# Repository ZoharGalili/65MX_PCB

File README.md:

# The65MX Keyboard PCB

a 65% keyboard pcb for use with my future keyboard projects.

## Features

### big components and BAV-70 diodes

I plan to assemble the pcb by hand to save costs as I have no problem putting the time to solder commponents by hand. for this reason i chose to not have any footprints smaller than an 0805 and also use BAV-70 dual diodes as i belive it will take less time to solder a single BAV-70 than two standard diodes.

### JST_SH daughterboard connector

I like the UBD-S daughterboard for case design but I have learned from a previous keyboard project that the molex EZmate connector is shit. I probably didnt solder it properly and it repeatedly snapped of the board. for this exact reason I desined the [UBD-S-JST](https://github.com/ZoharGalili/UDB-S-JST), a fork of the [UBD-S](https://github.com/Unified-Daughterboard/UDB-S) with a JST connecotr along with some ohter changes.

### QMK firmware and VIA support

the PCB uses an STM32f072 microcontroller. I have made a keyboard with this microcontroller before running QMK with VIA 

### bakeneko65 and ai03 vega board outline

I coppied the board outline of the bekeneko for supporting a gummy o-ring friction fit mount. I also took the board outline from the ai03 vega so the board can support an internally screwed case. 

### soldered MX switches

I have encountered problems before with the standard keilh hot swap sockets so i decided to make a solder pcb this time. mill max sockets exits so if I ever want to have a hotswap board I can pop those in.

### multilatout support

the board supports 6.25u or 7u spacebar, stepped caps lock and split backspace. this isnt the most layouts in a board but i feel like those are the layouts that I may want to use and I dont want to go crazy with layout support.

## board renders

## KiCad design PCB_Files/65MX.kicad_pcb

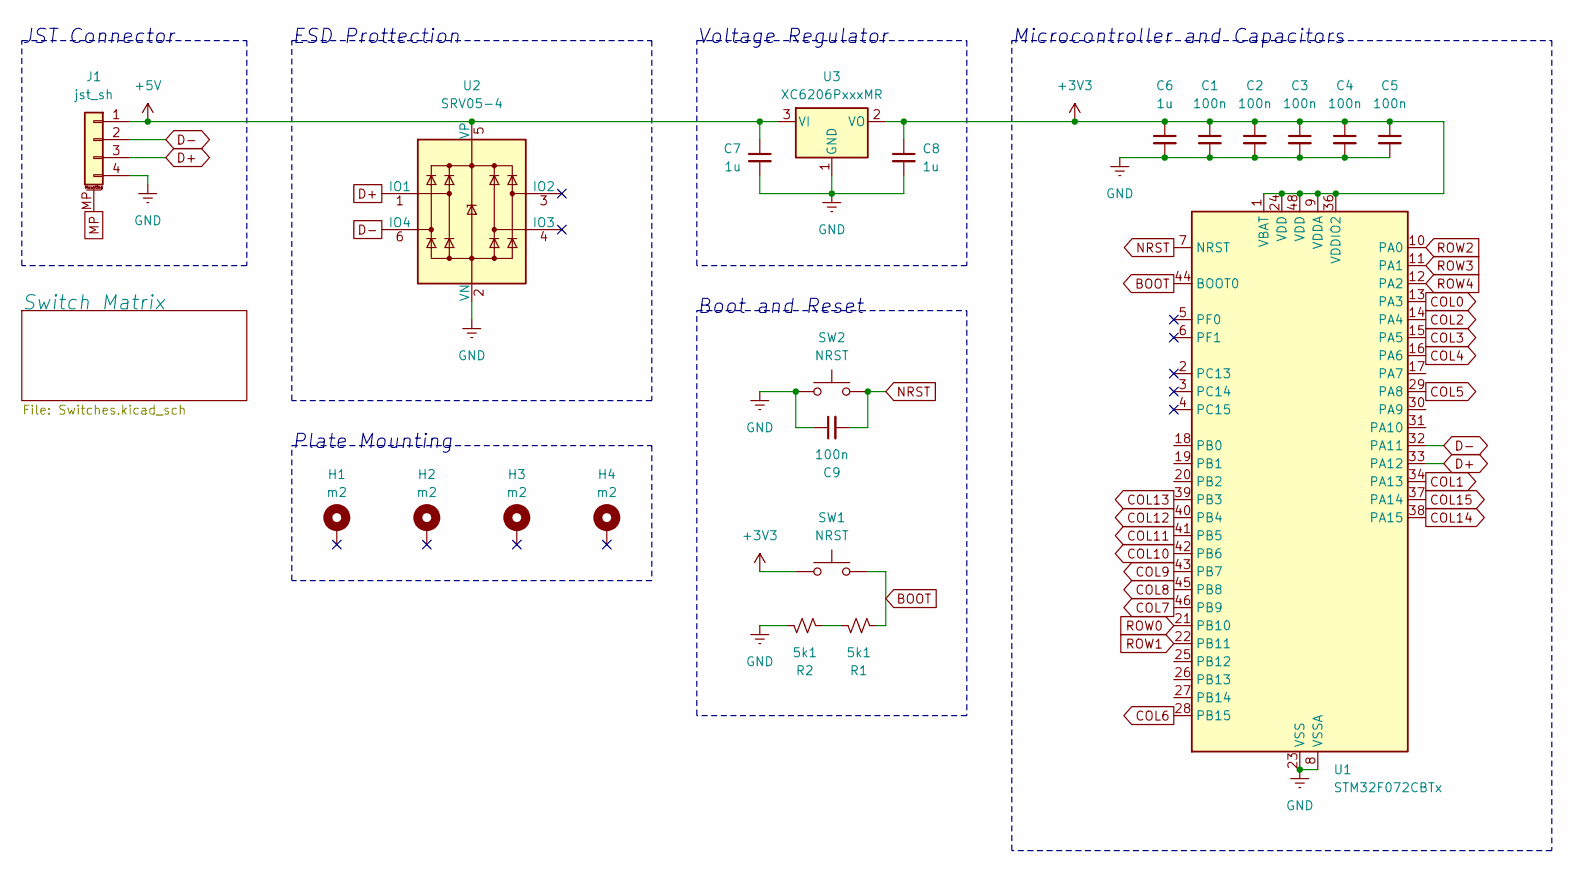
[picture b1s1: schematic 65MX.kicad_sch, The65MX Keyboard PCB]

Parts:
C1, C2, C3, C4, C5, C9: 100n; C_0805_2012Metric
C6, C7, C8: 1u; C_1206_3216Metric
H1, H2, H3, H4: m2; MountingHole_2.2mm_M2_Pad_TopBottom
J1: jst_sh; JST_SH_SM04B-SRSS-TB_1x04-1MP_P1.00mm_Horizontal
R1, R2: 5k1; R_0805_2012Metric
SW1, SW2: NRST; SW_SPST_SKQG_WithStem
U1: STM32F072CBTx; LQFP-48_7x7mm_P0.5mm
U2: SRV05-4; SOT-23-6-routable
U3: XC6206PxxxMR; SOT-23-3

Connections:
+3V3: C1.1, C2.1, C3.1, C4.1, C5.1, C6.1, C8.1, SW1.1, U1.1 (VBAT), U1.9 (VDDA), U1.24 (VDD), U1.36 (VDDIO2), U1.48 (VDD), U3.2 (VO)
+5V: C7.1, J1.1, U2.5 (VP), U3.3 (VI)
BOOT: R1.2, SW1.2, U1.44 (BOOT0)
COL0: U1.13 (PA3); also elsewhere on the board
COL1: U1.34 (PA13); also elsewhere on the board
COL2: U1.14 (PA4); also elsewhere on the board
COL3: U1.15 (PA5); also elsewhere on the board
COL4: U1.16 (PA6); also elsewhere on the board
COL5: U1.29 (PA8); also elsewhere on the board
COL6: U1.28 (PB15); also elsewhere on the board
COL7: U1.46 (PB9); also elsewhere on the board
COL8: U1.45 (PB8); also elsewhere on the board
COL9: U1.43 (PB7); also elsewhere on the board
COL10: U1.42 (PB6); also elsewhere on the board
COL11: U1.41 (PB5); also elsewhere on the board
COL12: U1.40 (PB4); also elsewhere on the board
COL13: U1.39 (PB3); also elsewhere on the board
COL14: U1.38 (PA15); also elsewhere on the board
COL15: U1.37 (PA14); also elsewhere on the board
D+: J1.3, U1.33 (PA12), U2.1 (IO1)
D-: J1.2, U1.32 (PA11), U2.6 (IO4)
GND: C1.2, C2.2, C3.2, C4.2, C5.2, C6.2, C7.2, C8.2, C9.1, J1.4, R2.1, SW2.1, U1.8 (VSSA), U1.23 (VSS), U1.35 (VSS), U1.47 (VSS), U2.2 (VN), U3.1 (GND)
MP: J1.MP (MountPin)
NRST: C9.2, SW2.2, U1.7 (NRST)
unnamed: R1.1, R2.2
ROW0: U1.21 (PB10); also elsewhere on the board
ROW1: U1.22 (PB11); also elsewhere on the board
ROW2: U1.10 (PA0); also elsewhere on the board
ROW3: U1.11 (PA1); also elsewhere on the board
ROW4: U1.12 (PA2); also elsewhere on the board

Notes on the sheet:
Microcontroller and Capacitors
Voltage Regulator
JST Connector
ESD Prottection
Plate Mounting
Boot and Reset

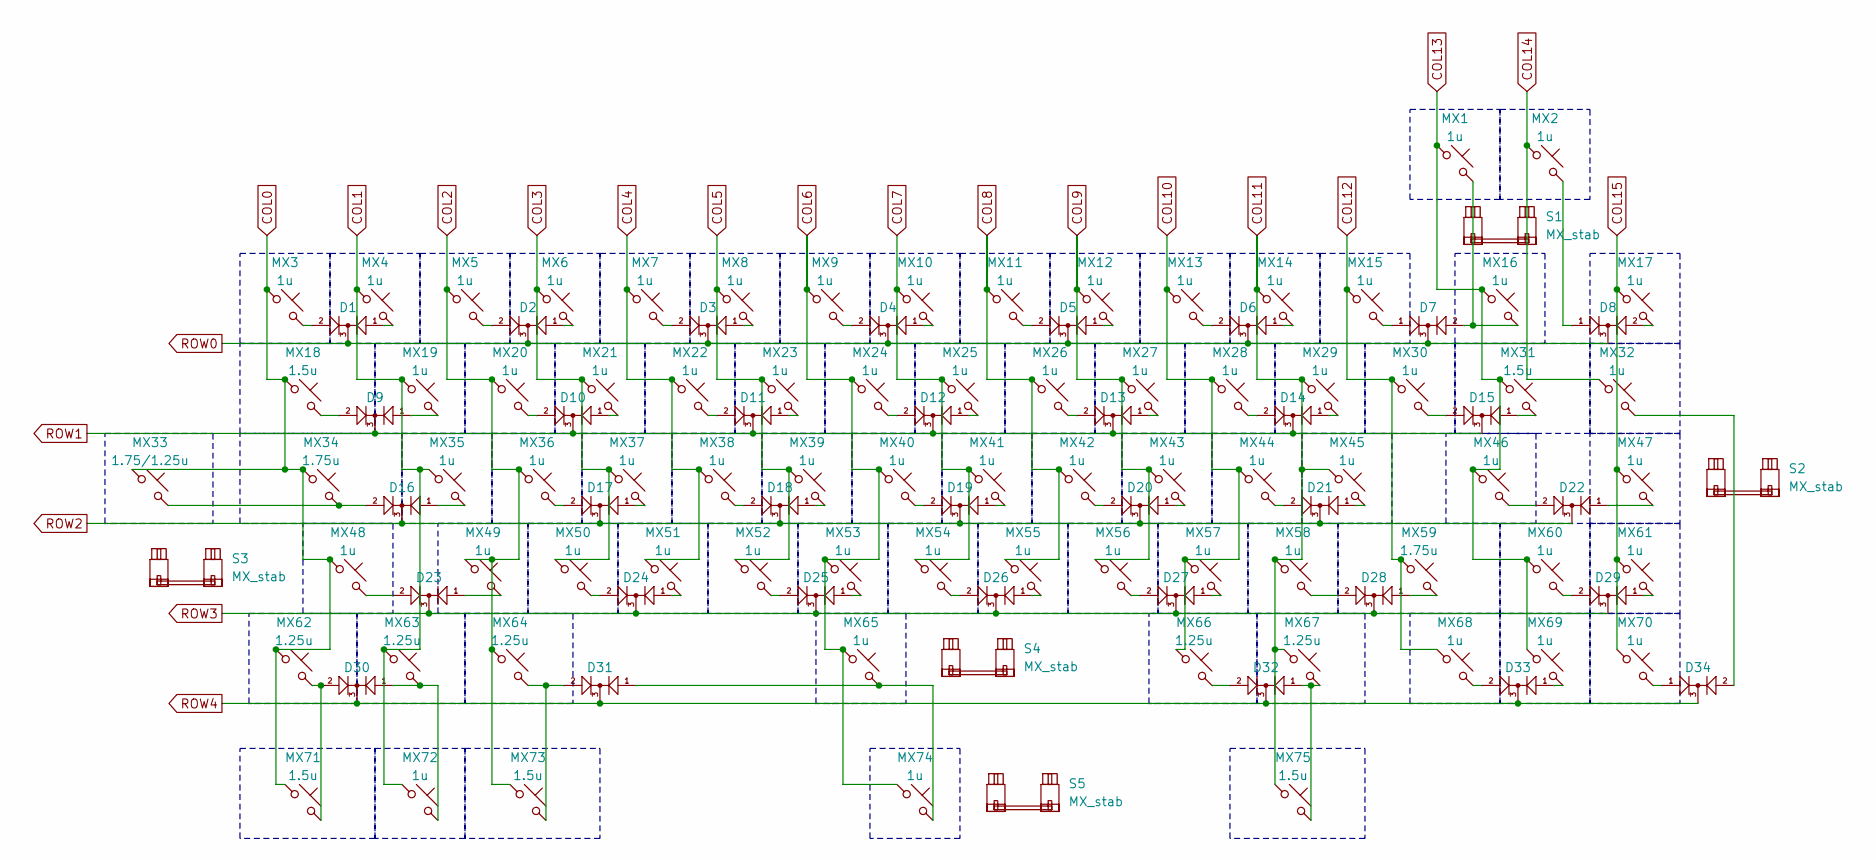
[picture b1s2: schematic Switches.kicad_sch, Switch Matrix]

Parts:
D1, D2, D3, D4, D5, D6, D7, D8, D9, D10, D11, D12, D13, D14, D15, D16, D17, D18, D19, D20, D21, D22, D23, D24, D25, D26, D27, D28, D29, D30, D31, D32, D33, D34: BAV70_Small; SOT-23
MX1, MX2, MX3, MX4, MX5, MX6, MX7, MX8, MX9, MX10, MX11, MX12, MX13, MX14, MX15, MX16, MX17, MX19, MX20, MX21, MX22, MX23, MX24, MX25, MX26, MX27, MX28, MX29, MX30, MX32, MX35, MX36, MX37, MX38, MX39, MX40, MX41, MX42, MX43, MX44, MX45, MX46, MX47, MX48, MX49, MX50, MX51, MX52, MX53, MX54, MX55, MX56, MX57, MX58, MX60, MX61, MX65, MX68, MX69, MX70, MX72, MX74: 1u; SW_MX_1u
MX18, MX31, MX71, MX73, MX75: 1.5u; SW_MX_1.5u
MX33: 1.75/1.25u; SW_MX_1.75u_STP_1.25
MX34, MX59: 1.75u; SW_MX_1.75u
MX62, MX63, MX64, MX66, MX67: 1.25u; SW_MX_1.25u
S1: MX_stab; STAB_MX_P_2u
S2, S3: MX_stab; STAB_MX_P_2.25u
S4: MX_stab; STAB_MX_P_6.25u
S5: MX_stab; STAB_MX_P_7u

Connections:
COL0: MX3.1, MX18.1, MX33.1, MX34.1, MX48.1, MX62.1, MX71.1; also elsewhere on the board
COL1: MX4.1, MX19.1, MX35.1, MX63.1, MX72.1; also elsewhere on the board
COL2: MX5.1, MX20.1, MX36.1, MX49.1, MX64.1, MX73.1; also elsewhere on the board
COL3: MX6.1, MX21.1, MX37.1, MX50.1; also elsewhere on the board
COL4: MX7.1, MX22.1, MX38.1, MX51.1; also elsewhere on the board
COL5: MX8.1, MX23.1, MX39.1, MX52.1; also elsewhere on the board
COL6: MX9.1, MX24.1, MX40.1, MX53.1, MX65.1, MX74.1; also elsewhere on the board
COL7: MX10.1, MX25.1, MX41.1, MX54.1; also elsewhere on the board
COL8: MX11.1, MX26.1, MX42.1, MX55.1; also elsewhere on the board
COL9: MX12.1, MX27.1, MX43.1, MX56.1; also elsewhere on the board
COL10: MX13.1, MX28.1, MX44.1, MX57.1, MX66.1; also elsewhere on the board
COL11: MX14.1, MX29.1, MX45.1, MX58.1, MX67.1, MX75.1; also elsewhere on the board
COL12: MX15.1, MX30.1, MX59.1, MX68.1; also elsewhere on the board
COL13: MX1.1, MX16.1, MX31.1, MX46.1, MX60.1, MX69.1; also elsewhere on the board
COL14: MX2.1, MX32.1; also elsewhere on the board
COL15: MX17.1, MX47.1, MX61.1, MX70.1; also elsewhere on the board
unnamed: D1.1 (A1), MX4.2
unnamed: D1.2 (A2), MX3.2
unnamed: D2.1 (A1), MX6.2
unnamed: D2.2 (A2), MX5.2
unnamed: D3.1 (A1), MX8.2
unnamed: D3.2 (A2), MX7.2
unnamed: D4.1 (A1), MX10.2
unnamed: D4.2 (A2), MX9.2
unnamed: D5.1 (A1), MX12.2
unnamed: D5.2 (A2), MX11.2
unnamed: D6.1 (A1), MX14.2
unnamed: D6.2 (A2), MX13.2
unnamed: D7.1 (A1), MX15.2
unnamed: D7.2 (A2), MX1.2, MX16.2
unnamed: D8.1 (A1), MX2.2
unnamed: D8.2 (A2), MX17.2
unnamed: D9.1 (A1), MX19.2
unnamed: D9.2 (A2), MX18.2
unnamed: D10.1 (A1), MX21.2
unnamed: D10.2 (A2), MX20.2
unnamed: D11.1 (A1), MX23.2
unnamed: D11.2 (A2), MX22.2
unnamed: D12.1 (A1), MX25.2
unnamed: D12.2 (A2), MX24.2
unnamed: D13.1 (A1), MX27.2
unnamed: D13.2 (A2), MX26.2
unnamed: D14.1 (A1), MX29.2
unnamed: D14.2 (A2), MX28.2
unnamed: D15.1 (A1), MX31.2
unnamed: D15.2 (A2), MX30.2
unnamed: D16.1 (A1), MX35.2
unnamed: D16.2 (A2), MX33.2, MX34.2
unnamed: D17.1 (A1), MX37.2
unnamed: D17.2 (A2), MX36.2
unnamed: D18.1 (A1), MX39.2
unnamed: D18.2 (A2), MX38.2
unnamed: D19.1 (A1), MX41.2
unnamed: D19.2 (A2), MX40.2
unnamed: D20.1 (A1), MX43.2
unnamed: D20.2 (A2), MX42.2
unnamed: D21.1 (A1), MX45.2
unnamed: D21.2 (A2), MX44.2
unnamed: D22.1 (A1), MX47.2
unnamed: D22.2 (A2), MX46.2
unnamed: D23.1 (A1), MX49.2
unnamed: D23.2 (A2), MX48.2
unnamed: D24.1 (A1), MX51.2
unnamed: D24.2 (A2), MX50.2
unnamed: D25.1 (A1), MX53.2
unnamed: D25.2 (A2), MX52.2
unnamed: D26.1 (A1), MX55.2
unnamed: D26.2 (A2), MX54.2
unnamed: D27.1 (A1), MX57.2
unnamed: D27.2 (A2), MX56.2
unnamed: D28.1 (A1), MX59.2
unnamed: D28.2 (A2), MX58.2
unnamed: D29.1 (A1), MX61.2
unnamed: D29.2 (A2), MX60.2
unnamed: D30.1 (A1), MX63.2, MX72.2
unnamed: D30.2 (A2), MX62.2, MX71.2
unnamed: D31.1 (A1), MX65.2, MX74.2
unnamed: D31.2 (A2), MX64.2, MX73.2
unnamed: D32.1 (A1), MX67.2, MX75.2
unnamed: D32.2 (A2), MX66.2
unnamed: D33.1 (A1), MX69.2
unnamed: D33.2 (A2), MX68.2
unnamed: D34.1 (A1), MX70.2
unnamed: D34.2 (A2), MX32.2
ROW0: D1.3 (K), D2.3 (K), D3.3 (K), D4.3 (K), D5.3 (K), D6.3 (K), D7.3 (K), D8.3 (K); also elsewhere on the board
ROW1: D9.3 (K), D10.3 (K), D11.3 (K), D12.3 (K), D13.3 (K), D14.3 (K), D15.3 (K); also elsewhere on the board
ROW2: D16.3 (K), D17.3 (K), D18.3 (K), D19.3 (K), D20.3 (K), D21.3 (K), D22.3 (K); also elsewhere on the board
ROW3: D23.3 (K), D24.3 (K), D25.3 (K), D26.3 (K), D27.3 (K), D28.3 (K), D29.3 (K); also elsewhere on the board
ROW4: D30.3 (K), D31.3 (K), D32.3 (K), D33.3 (K), D34.3 (K); also elsewhere on the board

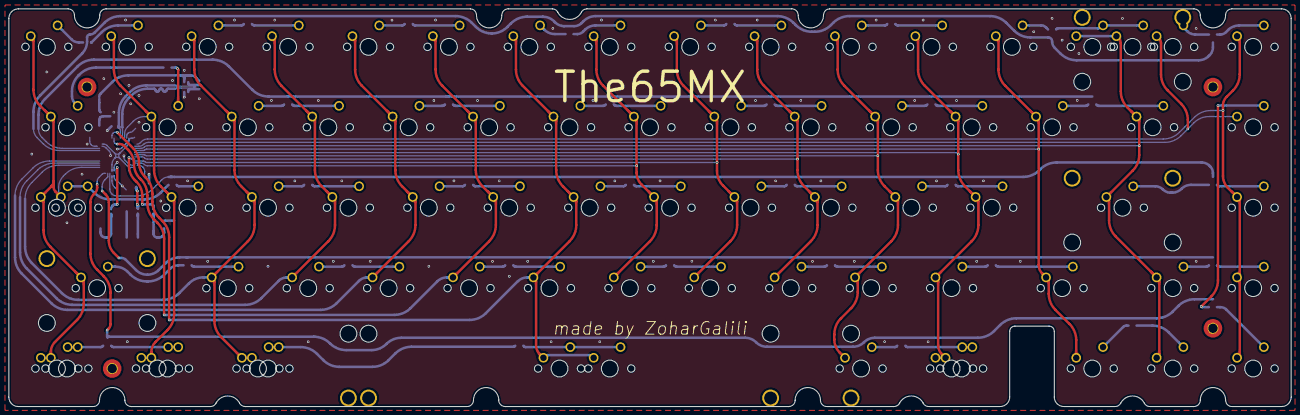
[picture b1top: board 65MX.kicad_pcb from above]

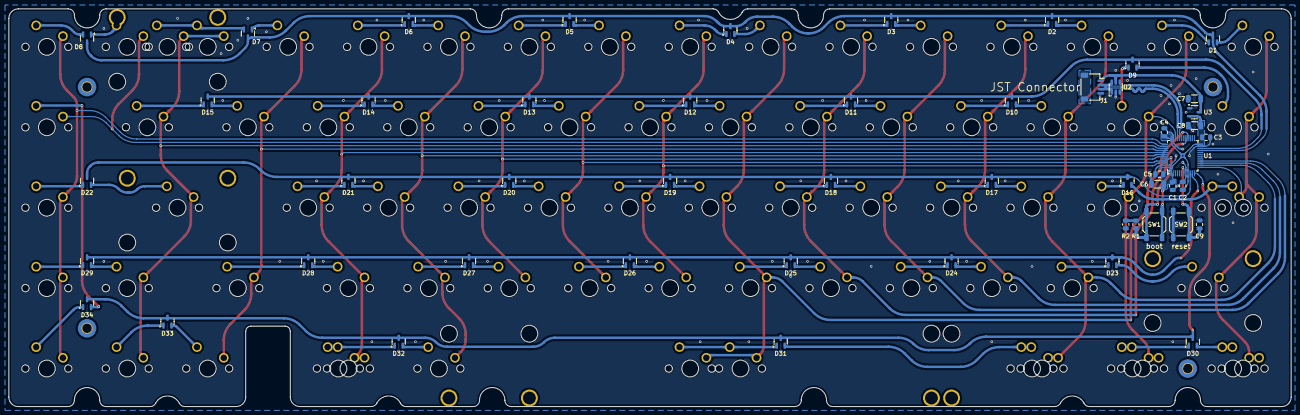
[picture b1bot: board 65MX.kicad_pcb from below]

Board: 2 copper layers, 303.8 x 94.2 mm, 135 parts (51 on the bottom side), 97 nets.

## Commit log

2025-11-28 made a pcb!
2025-11-29 made a readme
2025-12-02 Boot+Reset silkscreen
    added a silkscreen next to the boot and reset switches to differentiate between then
2025-12-03 moved plate holes
    moved plate holes to enable proper gummy o ring mounting
2026-03-05 added firmware
    added the qmk firmware files to the repo
2026-03-06 fixed firmware
    via is fully working now
2026-03-23 added boot keycode
